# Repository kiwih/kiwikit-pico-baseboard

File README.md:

# Kiwikit Pico Baseboard

This board provides an easy-to-solder all-throughole 10cm x 10cm 2-layer board which is used in conjunction with a Raspberry Pi Pico for basic, fun experimentation!

Features include:
* Three general purpose buttons and a reset button,
* Two general purpose LEDs and a power LED,
* An I2C SSD1306 Screen,
* An I2C AT24 EEPROM
* An LDR for Analog experimentation,
* And a bunch more expansion ports, two of which are arranged to work with cheap SD card and accelerometer modules!

## Usage

The latest schematic in PDF format, and the latest version of the gerbers for manufacture, are located directly 
in the root folder of this repository.

Alternatively, if you want to change any settings / etc, you can download this repository and open it with Kicad.
If so, you'll use this project in tandem with my `kiwih_kicad` Kicad repository: https://github.com/kiwih/kiwih_kicad

## Further documentation

I wrote a blog post to go with this! You can find it [here](https://01001000.xyz/2021-02-13-Raspberry-Pi-Pico-dev-board-Kiwikit/).

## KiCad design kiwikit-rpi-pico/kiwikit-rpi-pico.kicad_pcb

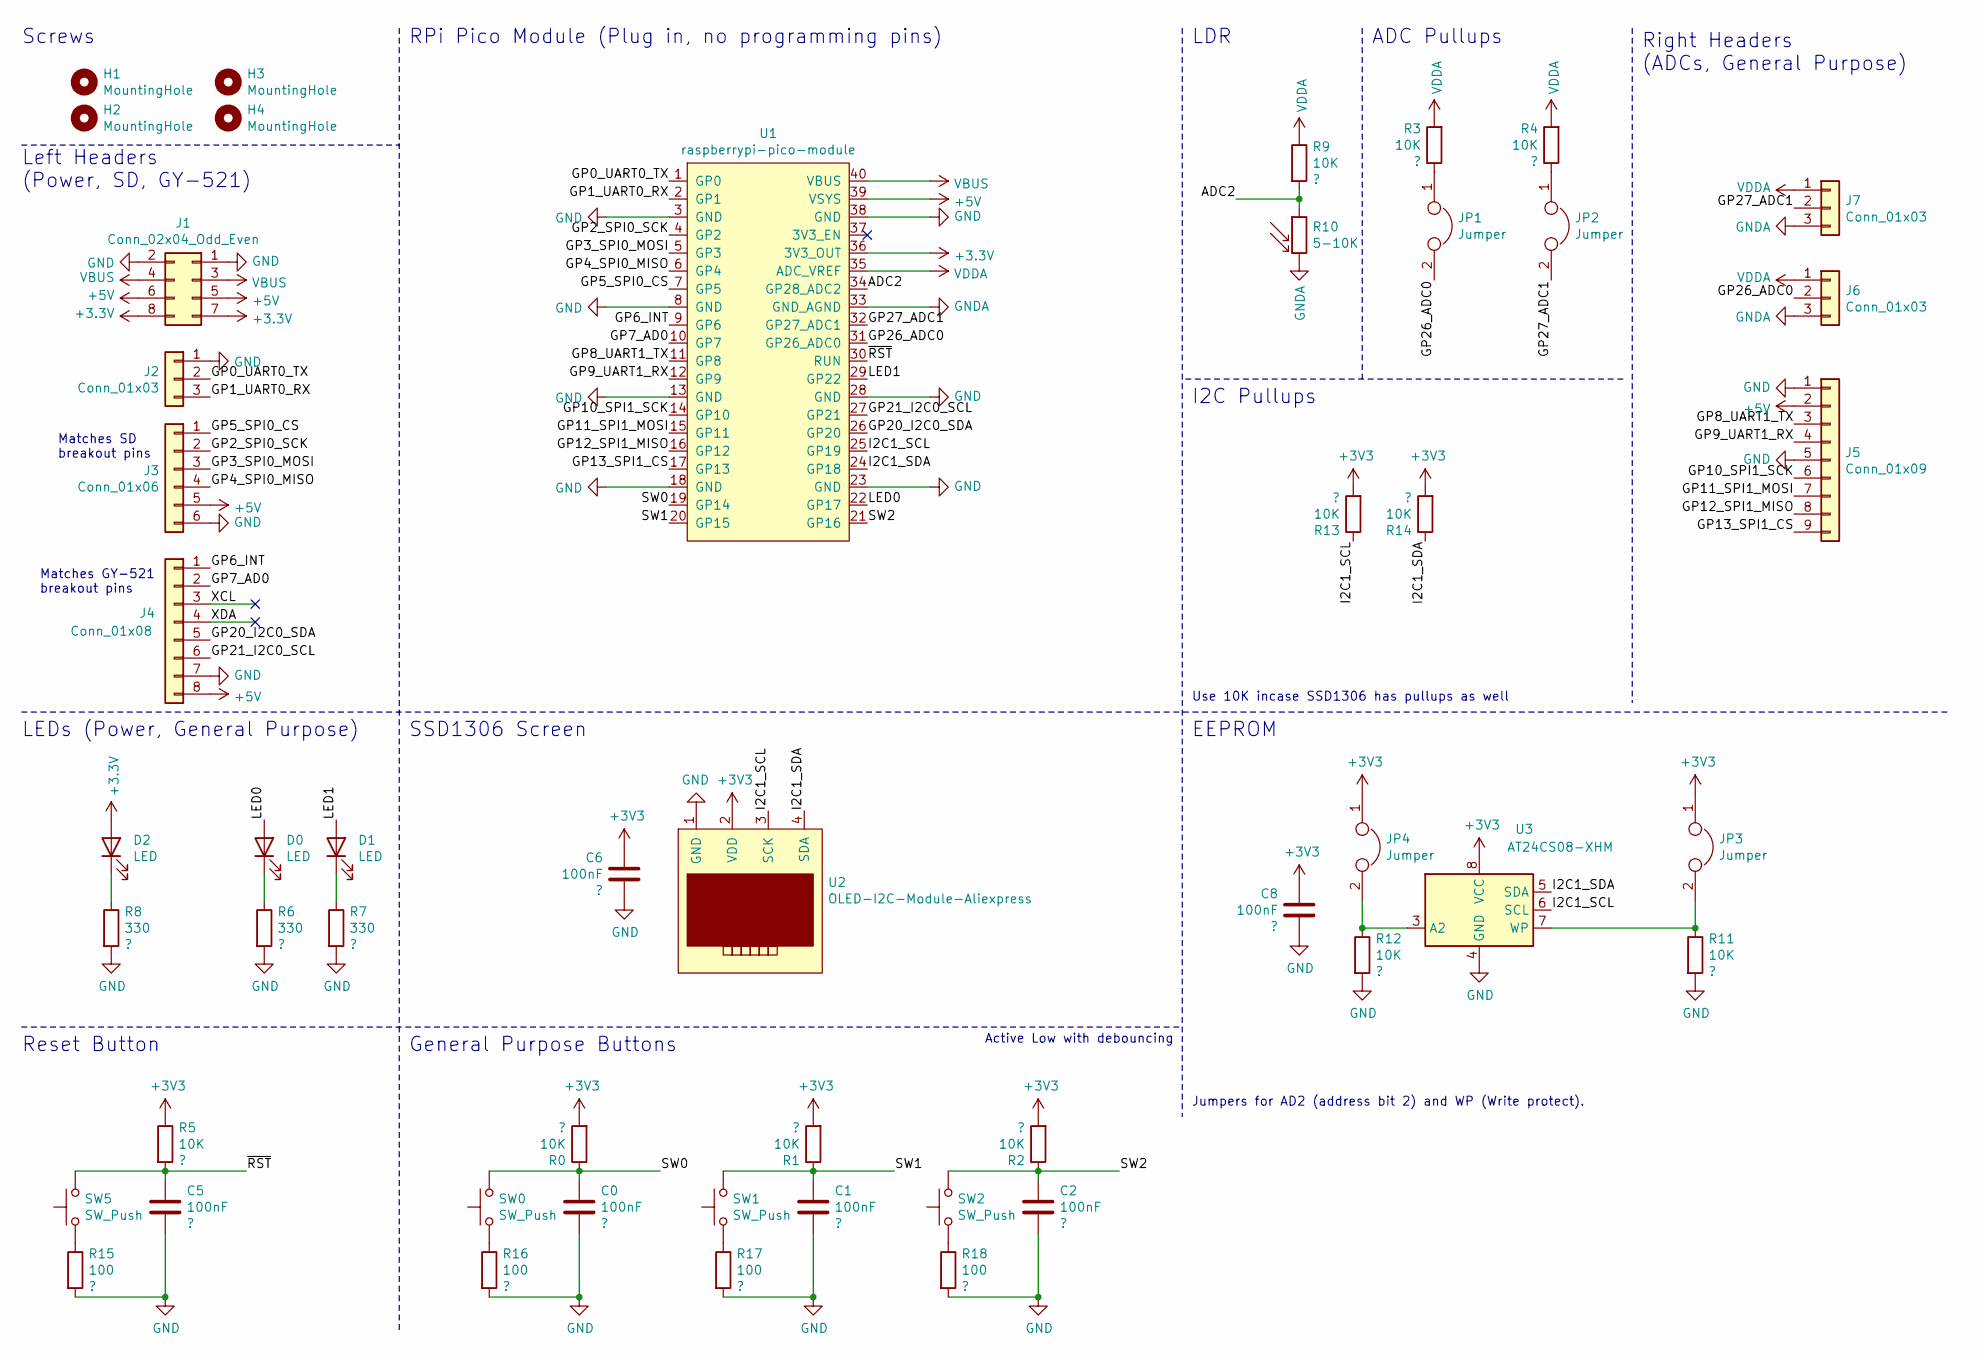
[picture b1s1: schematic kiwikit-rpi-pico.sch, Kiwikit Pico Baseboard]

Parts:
C0, C1, C2, C5, C6, C8: 100nF; C_Disc_D4.3mm_W1.9mm_P5.00mm
D0, D1, D2: LED; LED_D4.0mm
H1, H2, H3, H4: MountingHole; MountingHole_2.2mm_M2
J1: Conn_02x04_Odd_Even; PinHeader_2x04_P2.54mm_Vertical
J2, J6, J7: Conn_01x03; PinHeader_1x03_P2.54mm_Vertical
J3: Conn_01x06; PinSocket_1x06_P2.54mm_Vertical
J4: Conn_01x08; PinSocket_1x08_P2.54mm_Vertical
J5: Conn_01x09; PinHeader_1x09_P2.54mm_Vertical
JP1, JP2, JP3, JP4: Jumper; PinHeader_1x02_P2.54mm_Vertical
R0, R1, R2, R3, R4, R5, R9, R11, R12, R13, R14: 10K; R_Axial_DIN0207_L6.3mm_D2.5mm_P10.16mm_Horizontal
R6, R7, R8: 330; R_Axial_DIN0207_L6.3mm_D2.5mm_P10.16mm_Horizontal
R10: 5-10K; R_LDR_5.0x4.1mm_P3mm_Vertical
R15, R16, R17, R18: 100; R_Axial_DIN0207_L6.3mm_D2.5mm_P10.16mm_Horizontal
SW0, SW1, SW2: SW_Push; SW_PUSH_6mm_H9.5mm
SW5: SW_Push; SW_PUSH_6mm_H4.3mm
U1: raspberrypi-pico-module
U2: OLED-I2C-Module-Aliexpress
U3: AT24CS08-XHM; DIP-8_W7.62mm

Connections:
+5V: J1.5, J1.6, J3.5, J4.8, J5.2, U1.39 (VSYS)
/ADC2: R9.2, R10.1, U1.34 (GP28_ADC2)
/GP0_UART0_TX: J2.2, U1.1 (GP0)
/GP1_UART0_RX: J2.3, U1.2 (GP1)
/GP2_SPI0_SCK: J3.2, U1.4 (GP2)
/GP3_SPI0_MOSI: J3.3, U1.5 (GP3)
/GP4_SPI0_MISO: J3.4, U1.6 (GP4)
/GP5_SPI0_CS: J3.1, U1.7 (GP5)
/GP6_INT: J4.1, U1.9 (GP6)
/GP7_AD0: J4.2, U1.10 (GP7)
/GP8_UART1_TX: J5.3, U1.11 (GP8)
/GP9_UART1_RX: J5.4, U1.12 (GP9)
/GP10_SPI1_SCK: J5.6, U1.14 (GP10)
/GP11_SPI1_MOSI: J5.7, U1.15 (GP11)
/GP12_SPI1_MISO: J5.8, U1.16 (GP12)
/GP13_SPI1_CS: J5.9, U1.17 (GP13)
/GP20_I2C0_SDA: J4.5, U1.26 (GP20)
/GP21_I2C0_SCL: J4.6, U1.27 (GP21)
/GP26_ADC0: J6.2, JP1.2, U1.31 (GP26_ADC0)
/GP27_ADC1: J7.2, JP2.2, U1.32 (GP27_ADC1)
/I2C1_SCL: R13.1, U1.25 (GP19), U2.3 (SCK), U3.6 (SCL)
/I2C1_SDA: R14.1, U1.24 (GP18), U2.4 (SDA), U3.5 (SDA)
/LED0: D0.2 (A), U1.22 (GP17)
/LED1: D1.2 (A), U1.29 (GP22)
/SW0: C0.2, R0.1, SW0.2, U1.19 (GP14)
/SW1: C1.2, R1.1, SW1.2, U1.20 (GP15)
/SW2: C2.2, R2.1, SW2.2, U1.21 (GP16)
/XCL: J4.3
/XDA: J4.4
/~RST: C5.2, R5.2, SW5.2, U1.30 (RUN)
GND: C0.1, C1.1, C2.1, C5.1, C6.2, C8.2, J1.1, J1.2, J2.1, J3.6, J4.7, J5.1, J5.5, R6.2, R7.2, R8.2, R11.2, R12.2, R15.2, R16.2, R17.2, R18.2, U1.3 (GND), U1.8 (GND), U1.13 (GND), U1.18 (GND), U1.23 (GND), U1.28 (GND), U1.38 (GND), U2.1 (GND), U3.4 (GND)
GNDA: J6.3, J7.3, R10.2, U1.33 (GND_AGND)
unnamed: D0.1 (K), R6.1
unnamed: D1.1 (K), R7.1
unnamed: D2.1 (K), R8.1
unnamed: JP1.1, R3.1
unnamed: JP2.1, R4.1
unnamed: JP3.2, R11.1, U3.7 (WP)
unnamed: JP4.2, R12.1, U3.3 (A2)
unnamed: R15.1, SW5.1
unnamed: R16.1, SW0.1
unnamed: R17.1, SW1.1
unnamed: R18.1, SW2.1
VBUS: J1.3, J1.4, U1.40 (VBUS)
VDDA: J6.1, J7.1, R3.2, R4.2, R9.1, U1.35 (ADC_VREF)

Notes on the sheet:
Matches SD breakout pins
Matches GY-521 breakout pins
I2C Pullups
Right Headers (ADCs, General Purpose)
LDR
EEPROM
SSD1306 Screen
General Purpose Buttons
Reset Button
LEDs (Power, General Purpose)
Left Headers (Power, SD, GY-521)
Screws
RPi Pico Module (Plug in, no programming pins)
ADC Pullups
Use 10K incase SSD1306 has pullups as well
Jumpers for AD2 (address bit 2) and WP (Write protect).
Active Low with debouncing

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
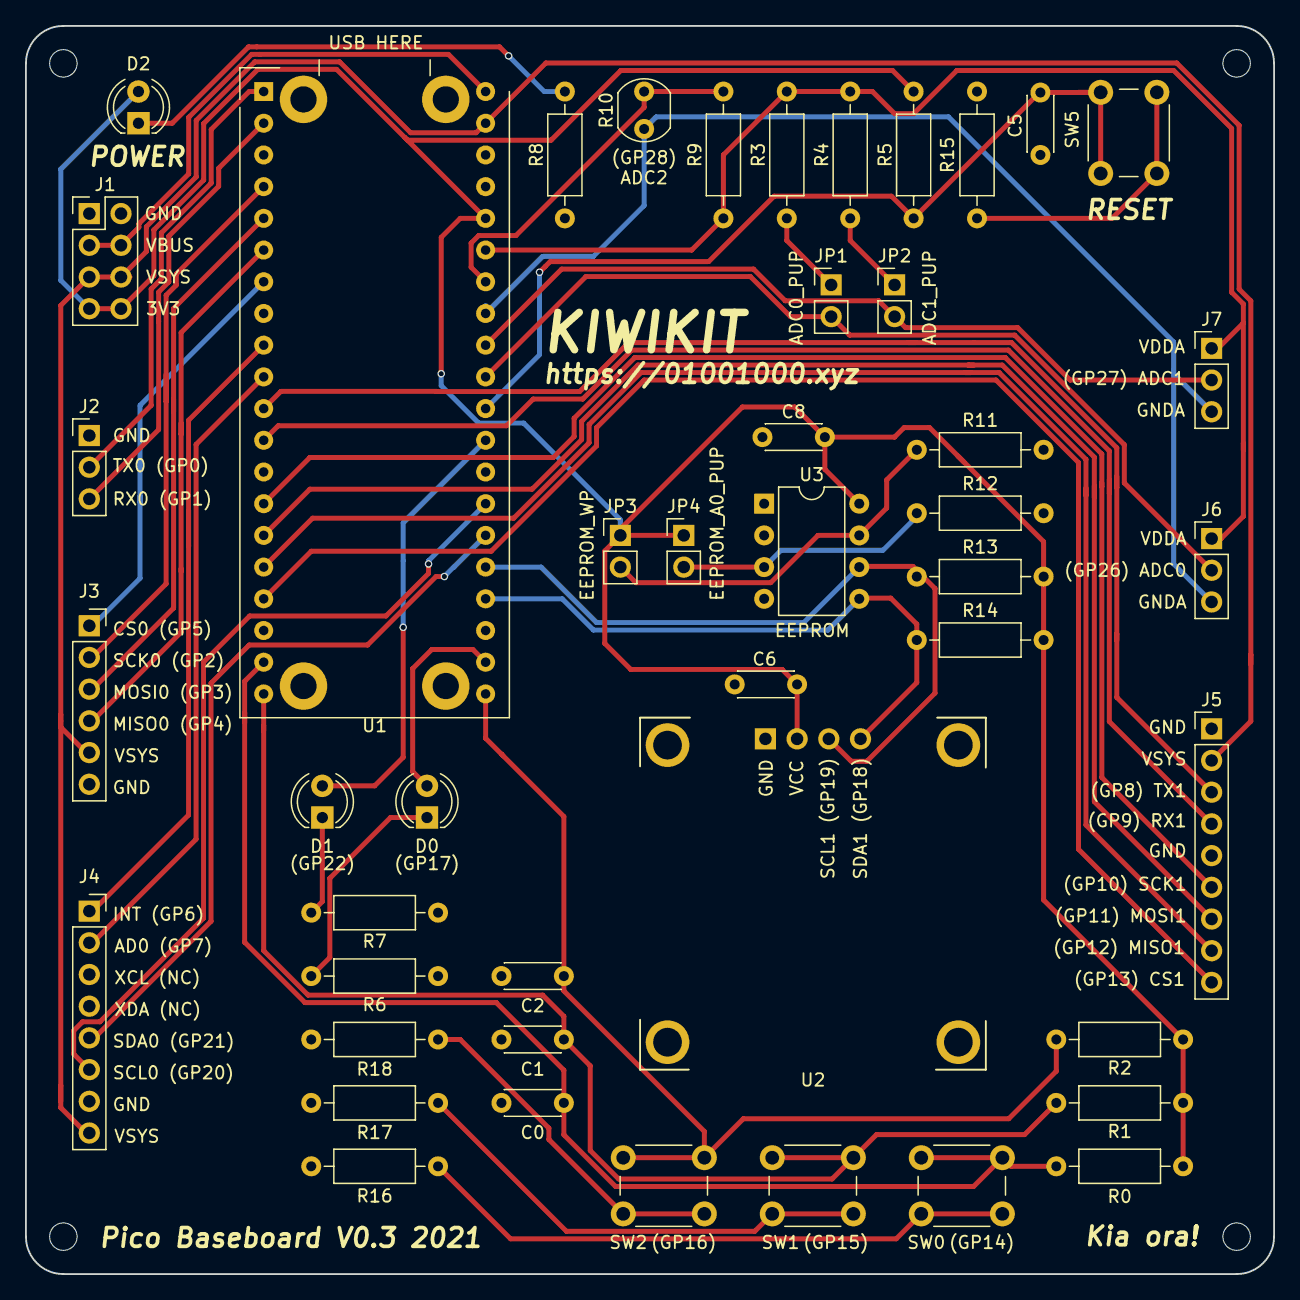
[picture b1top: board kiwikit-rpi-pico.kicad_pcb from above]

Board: 2 copper layers, 100.0 x 100.0 mm, 50 parts (0 on the bottom side), 44 nets.

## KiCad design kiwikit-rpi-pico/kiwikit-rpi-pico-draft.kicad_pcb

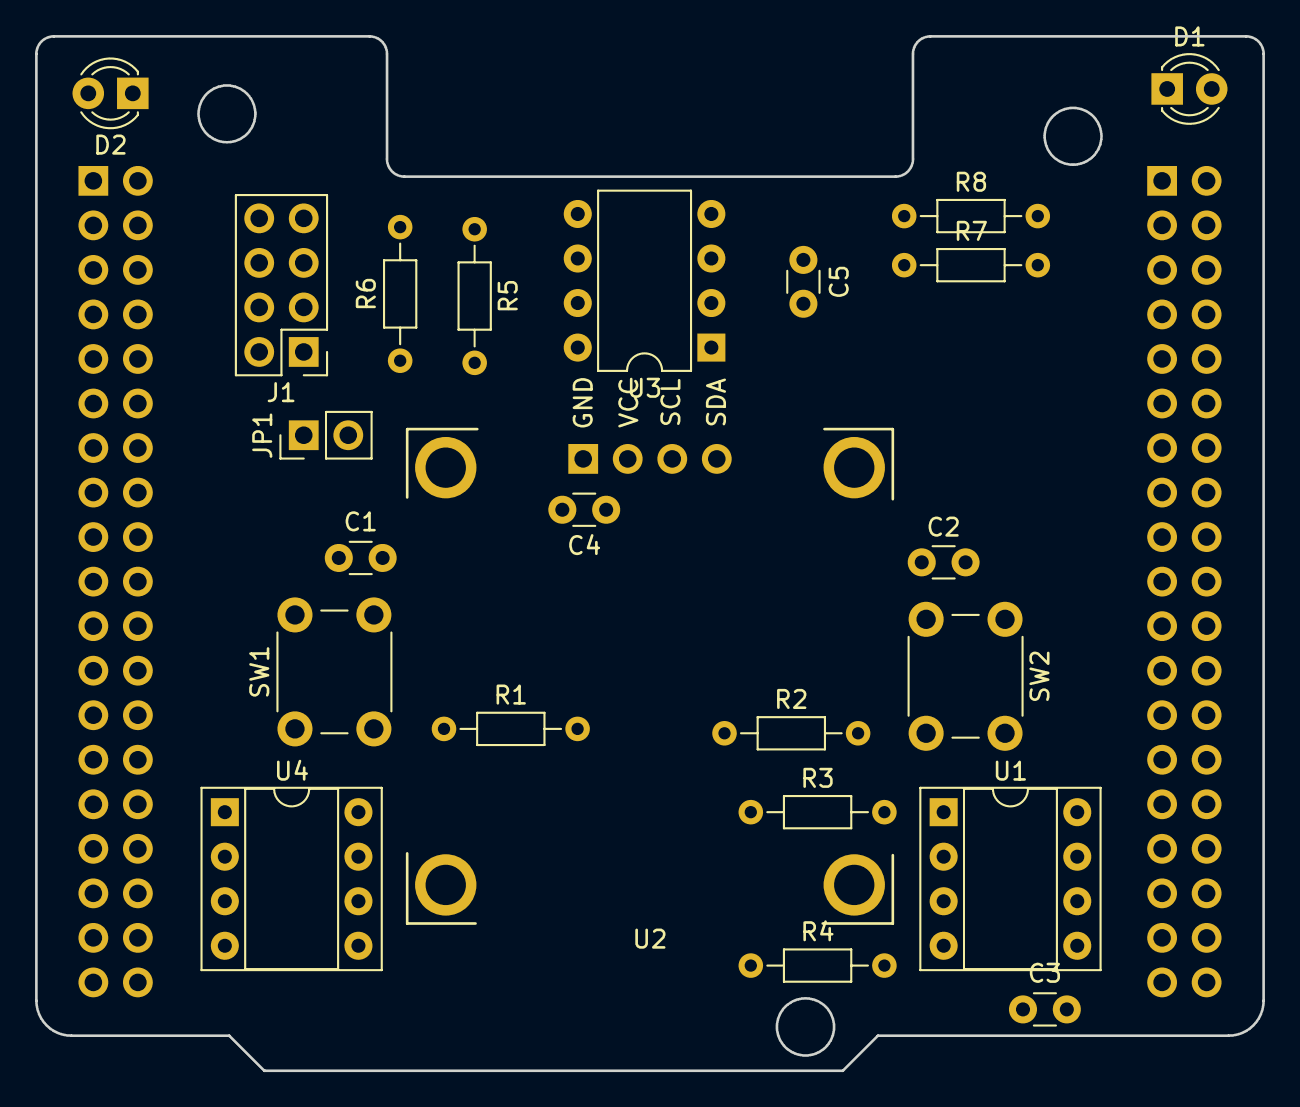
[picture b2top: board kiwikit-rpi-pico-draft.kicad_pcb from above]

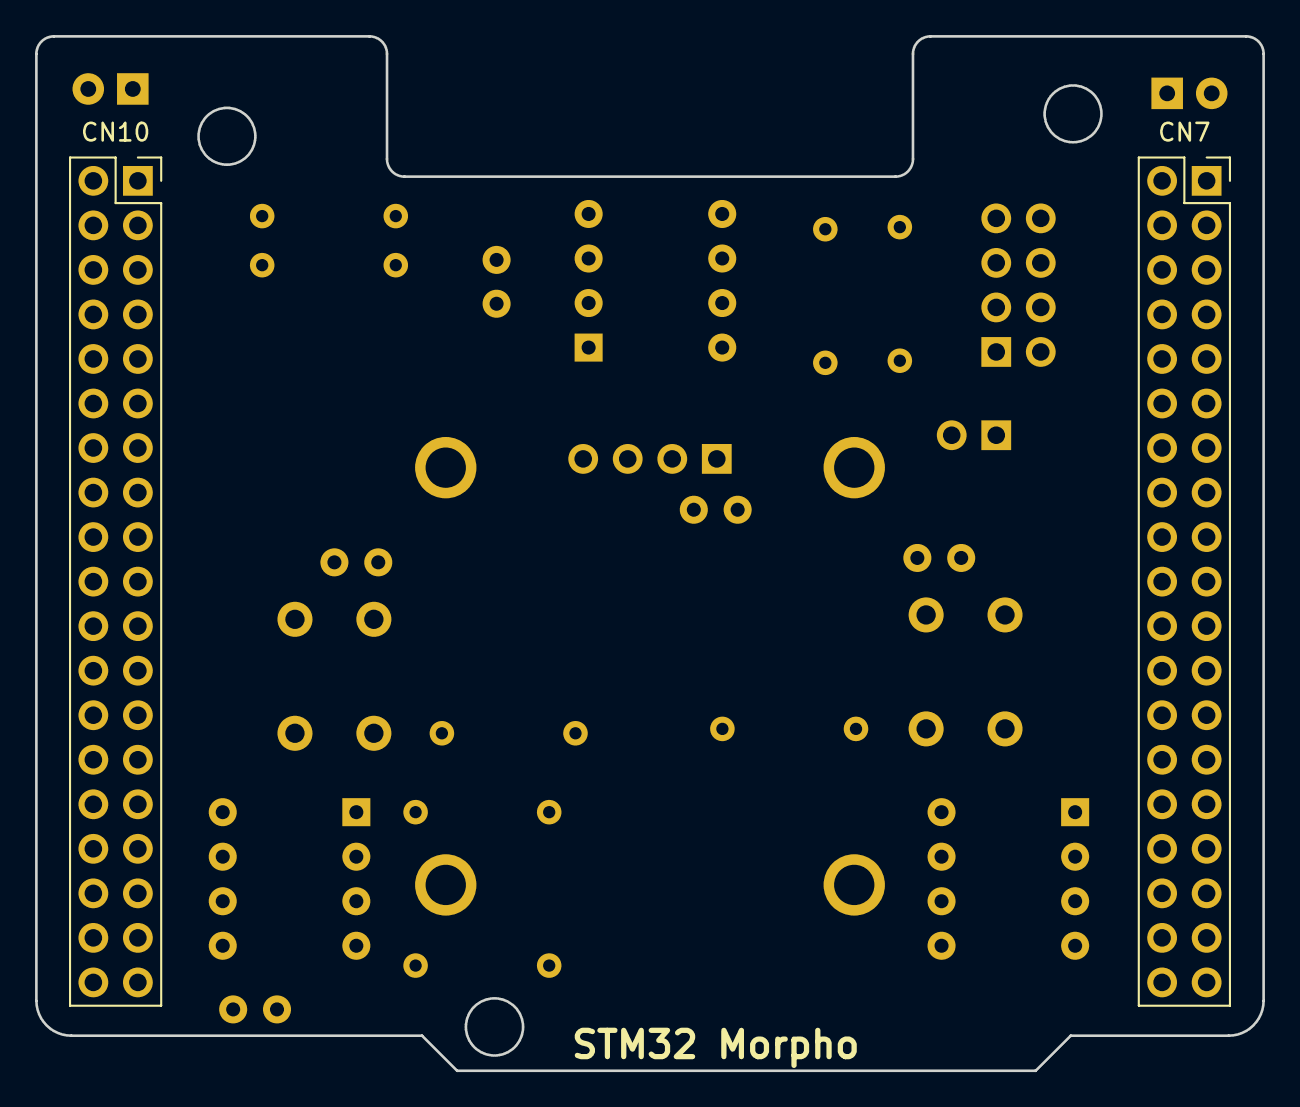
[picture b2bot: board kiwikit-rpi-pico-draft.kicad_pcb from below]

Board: 2 copper layers, 70.0 x 59.0 mm, 25 parts (2 on the bottom side), 22 nets, no tracks yet.

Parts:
C1, C2, C3, C4, C5: 100nF; C_Disc_D3.0mm_W1.6mm_P2.50mm
CN7, CN10: Conn_02x19_Odd_Even; PinSocket_2x19_P2.54mm_Vertical
D1, D2: LED; LED_D3.0mm
J1: Conn_02x04_Odd_Even; PinHeader_2x04_P2.54mm_Vertical
JP1: Jumper; PinHeader_1x02_P2.54mm_Vertical
R1, R2, R3, R4: 47K; R_Axial_DIN0204_L3.6mm_D1.6mm_P7.62mm_Horizontal
R5: 0; R_Axial_DIN0204_L3.6mm_D1.6mm_P7.62mm_Horizontal
R6: 120; R_Axial_DIN0204_L3.6mm_D1.6mm_P7.62mm_Horizontal
R7, R8: 470; R_Axial_DIN0204_L3.6mm_D1.6mm_P7.62mm_Horizontal
SW1, SW2: SW_Push; SW_PUSH_6mm_H4.3mm
U1: W25Q32JVSS; DIP-8_W7.62mm_Socket
U2: OLED-I2C-Module-Aliexpress
U3: MCP2551-I-P; DIP-8_W7.62mm
U4: AT24CS08-XHM; DIP-8_W7.62mm_Socket

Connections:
+3V3: C3.1, C4.1, C5.1, CN7.16, R1.1, R2.1, R3.1, R4.1, U1.8, U2.2, U4.8
+5V: CN7.18, U3.3
/CAN1_RD: CN10.3, U3.4
/CAN1_TD: CN10.5, U3.1
/CANH: J1.1, J1.2, JP1.1, U3.7
/CANL: J1.3, J1.4, R6.2, U3.6
/I2C1_SCL: CN7.17, U2.3, U4.6
/I2C1_SDA: CN7.15, U2.4, U4.5
/PC5: C2.2, CN10.6, R2.2, SW2.2
/PC6: C1.2, CN10.4, R1.2, SW1.2
/PC8: CN10.2, D1.2
/PC9: CN10.1, D2.2
/SPI3_MISO: CN7.2, U1.2
/SPI3_MOSI: CN7.3, U1.5
/SPI3_SCLK: CN7.1, U1.6
GND: C1.1, C2.1, C3.2, C4.2, C5.2, CN7.8, CN7.19, CN7.20, CN7.22, CN10.9, CN10.20, J1.5, J1.6, R5.2, R7.2, R8.2, SW1.1, SW2.1, U1.4, U2.1, U3.2, U4.4
unnamed: D1.1, R7.1
unnamed: D2.1, R8.1
unnamed: JP1.2, R6.1
unnamed: R3.2, U1.3
unnamed: R4.2, U1.7
unnamed: R5.1, U3.8

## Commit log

2021-02-13 First commit V0.2 - First public commit
2021-02-20 Update to version 0.3, adjust debouncer layout.
2021-02-20 Add v0.3 schematic pdf
2021-02-20 Fix missing link
2021-02-25 Generate v0.3 gerbers
2021-02-25 Make it easier to find prod files
2021-03-02 Update to fix missing gerber file
2021-04-08 Add some micropython example scripts
